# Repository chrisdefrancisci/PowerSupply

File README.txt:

Power Supply
from: 
http://musicfromouterspace.com/index.php?CATPARTNO=WALLWARTKIT&PROJARG=WALLWARTSUPPLY%2FWALLWARTSUPPLY.php&MAINTAB=SYNTHDIY&SONGID=NONE&VPW=1427&VPH=751

eurorack power cable (from A-100 Technical Details)
http://www.doepfer.de/a100_man/a100t_e.htm
2x5 ribbon cables seem to always be used

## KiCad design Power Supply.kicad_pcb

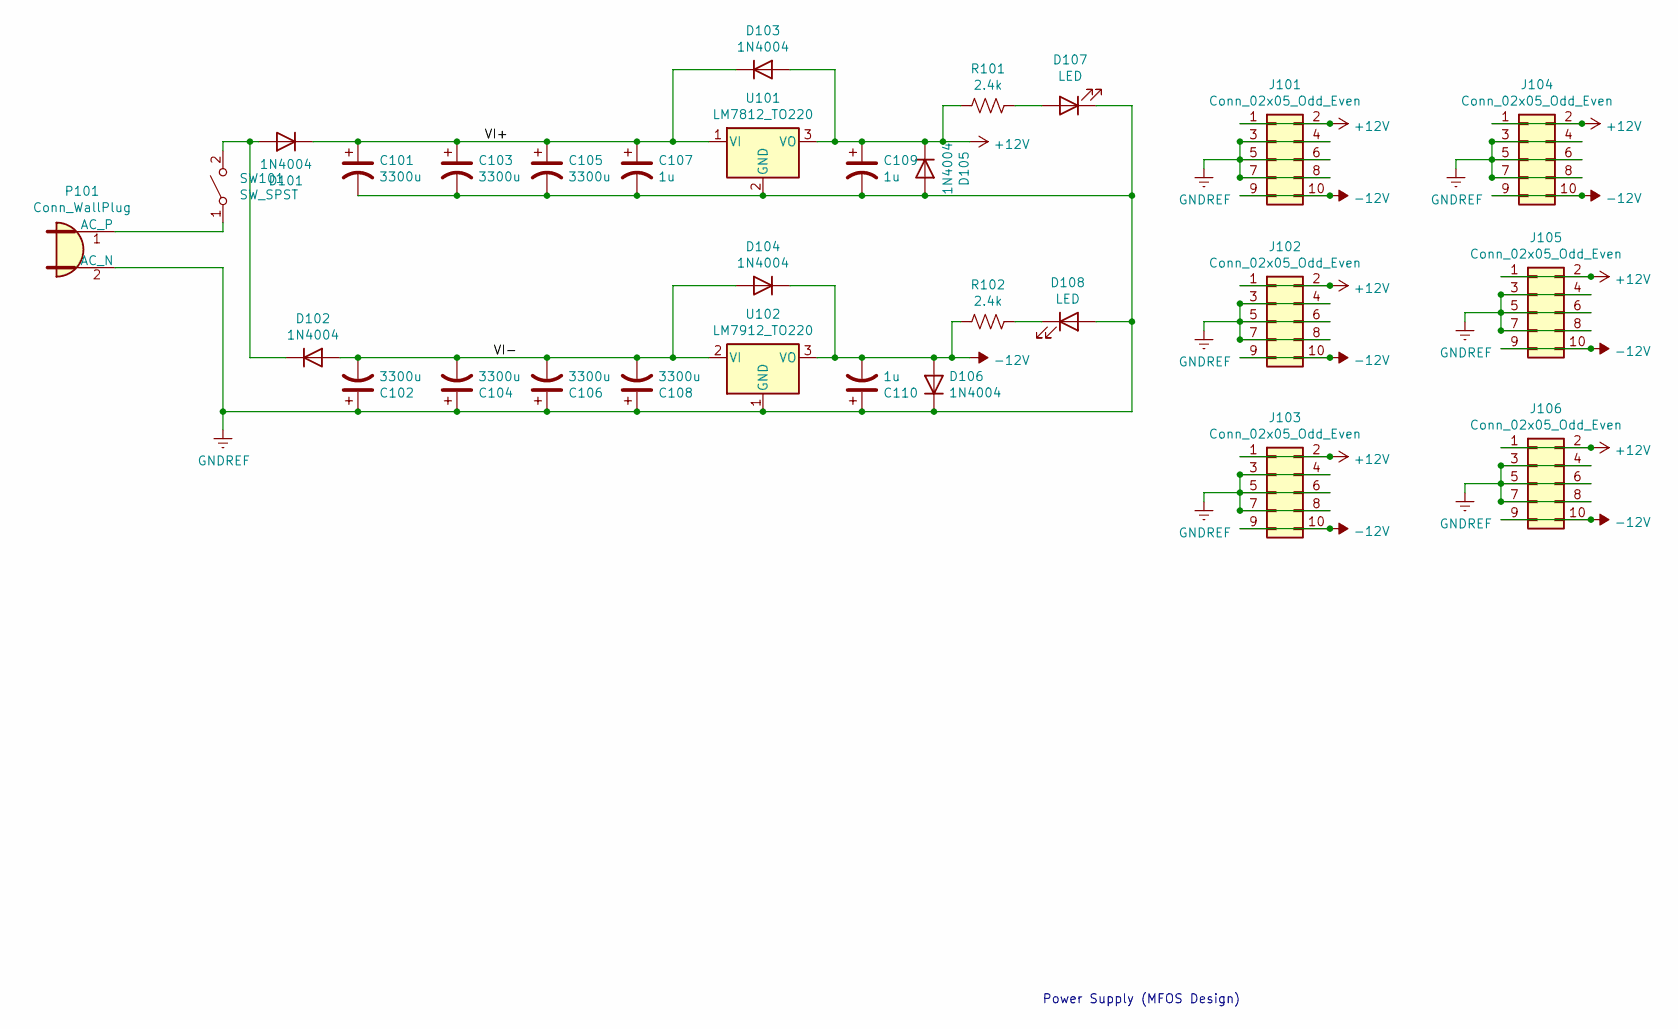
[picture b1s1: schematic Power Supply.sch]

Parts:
C101, C102, C103, C104, C105, C106: 3300u; CP_Radial_D16.0mm_P7.50mm
C107, C109, C110: 1u; CP_Radial_D5.0mm_P2.50mm
C108: 3300u; CP_Radial_D5.0mm_P2.50mm
D101, D102, D103, D104, D105, D106: 1N4004; D_DO-41_SOD81_P7.62mm_Horizontal
D107, D108: LED; LED_D5.0mm_Horizontal_O1.27mm_Z3.0mm
J101, J102, J103, J104, J105, J106: Conn_02x05_Odd_Even; PinHeader_2x05_P2.54mm_Vertical
P101: Conn_WallPlug; KLDHCX-0202-B
R101, R102: 2.4k; R_Axial_DIN0204_L3.6mm_D1.6mm_P2.54mm_Vertical
SW101: SW_SPST; RA1H1C112R
U101: LM7812_TO220; TO-220-3_Horizontal_TabDown
U102: LM7912_TO220; TO-220-3_Horizontal_TabDown

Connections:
+12V: C109.1, D103.2 (A), D105.1 (K), J101.1, J101.2, J102.1, J102.2, J103.1, J103.2, J104.1, J104.2, J105.1, J105.2, J106.1, J106.2, R101.2, U101.3 (VO)
-12V: C110.2, D104.1 (K), D106.2 (A), J101.9, J101.10, J102.9, J102.10, J103.9, J103.10, J104.9, J104.10, J105.9, J105.10, J106.9, J106.10, R102.2, U102.3 (VO)
/VI+: C101.1, C103.1, C105.1, C107.1, D101.1 (K), D103.1 (K), U101.1 (VI)
/VI-: C102.2, C104.2, C106.2, C108.2, D102.2 (A), D104.2 (A), U102.2 (VI)
GNDREF: C101.2, C102.1, C103.2, C104.1, C105.2, C106.1, C107.2, C108.1, C109.2, C110.1, D105.2 (A), D106.1 (K), D107.1 (K), D108.2 (A), J101.3, J101.4, J101.5, J101.6, J101.7, J101.8, J102.3, J102.4, J102.5, J102.6, J102.7, J102.8, J103.3, J103.4, J103.5, J103.6, J103.7, J103.8, J104.3, J104.4, J104.5, J104.6, J104.7, J104.8, J105.3, J105.4, J105.5, J105.6, J105.7, J105.8, J106.3, J106.4, J106.5, J106.6, J106.7, J106.8, P101.2 (AC_N), U101.2 (GND), U102.1 (GND)
unnamed: D101.2 (A), D102.1 (K), SW101.2 (B)
unnamed: D107.2 (A), R101.1
unnamed: D108.1 (K), R102.1
unnamed: P101.1 (AC_P), SW101.1 (A)

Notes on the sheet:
Power Supply (MFOS Design)

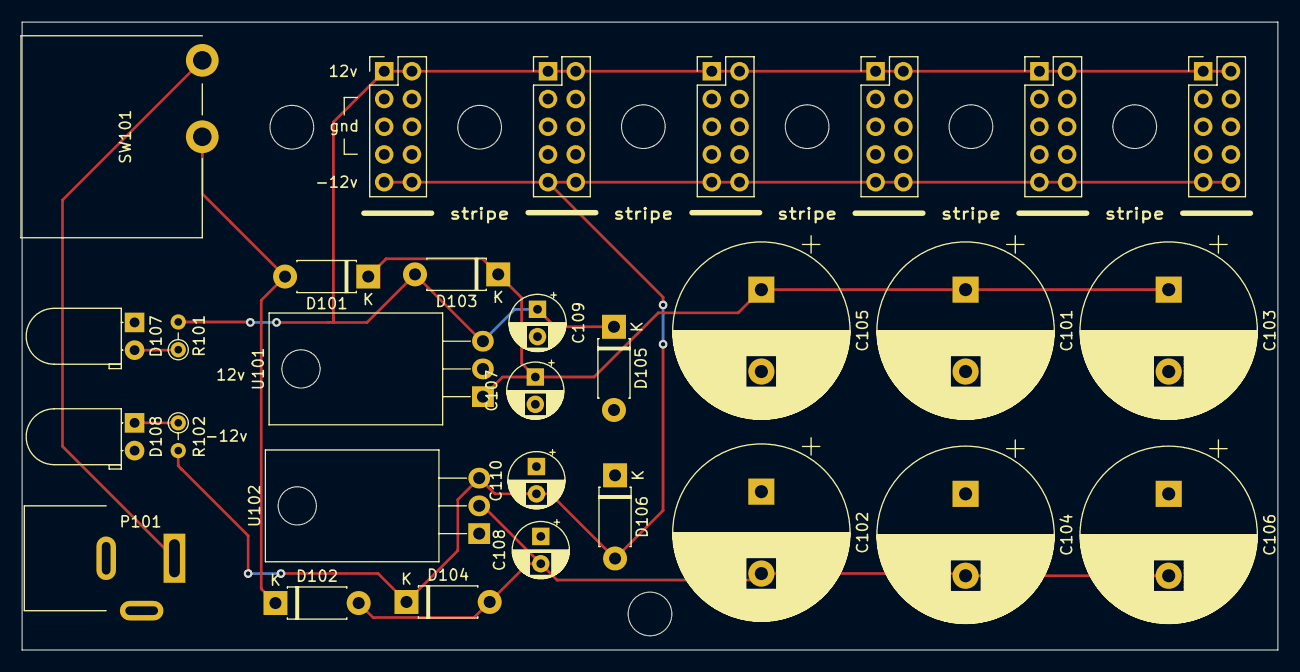
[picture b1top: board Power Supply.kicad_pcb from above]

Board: 2 copper layers, 115.0 x 57.5 mm, 30 parts (0 on the bottom side), 9 nets.
